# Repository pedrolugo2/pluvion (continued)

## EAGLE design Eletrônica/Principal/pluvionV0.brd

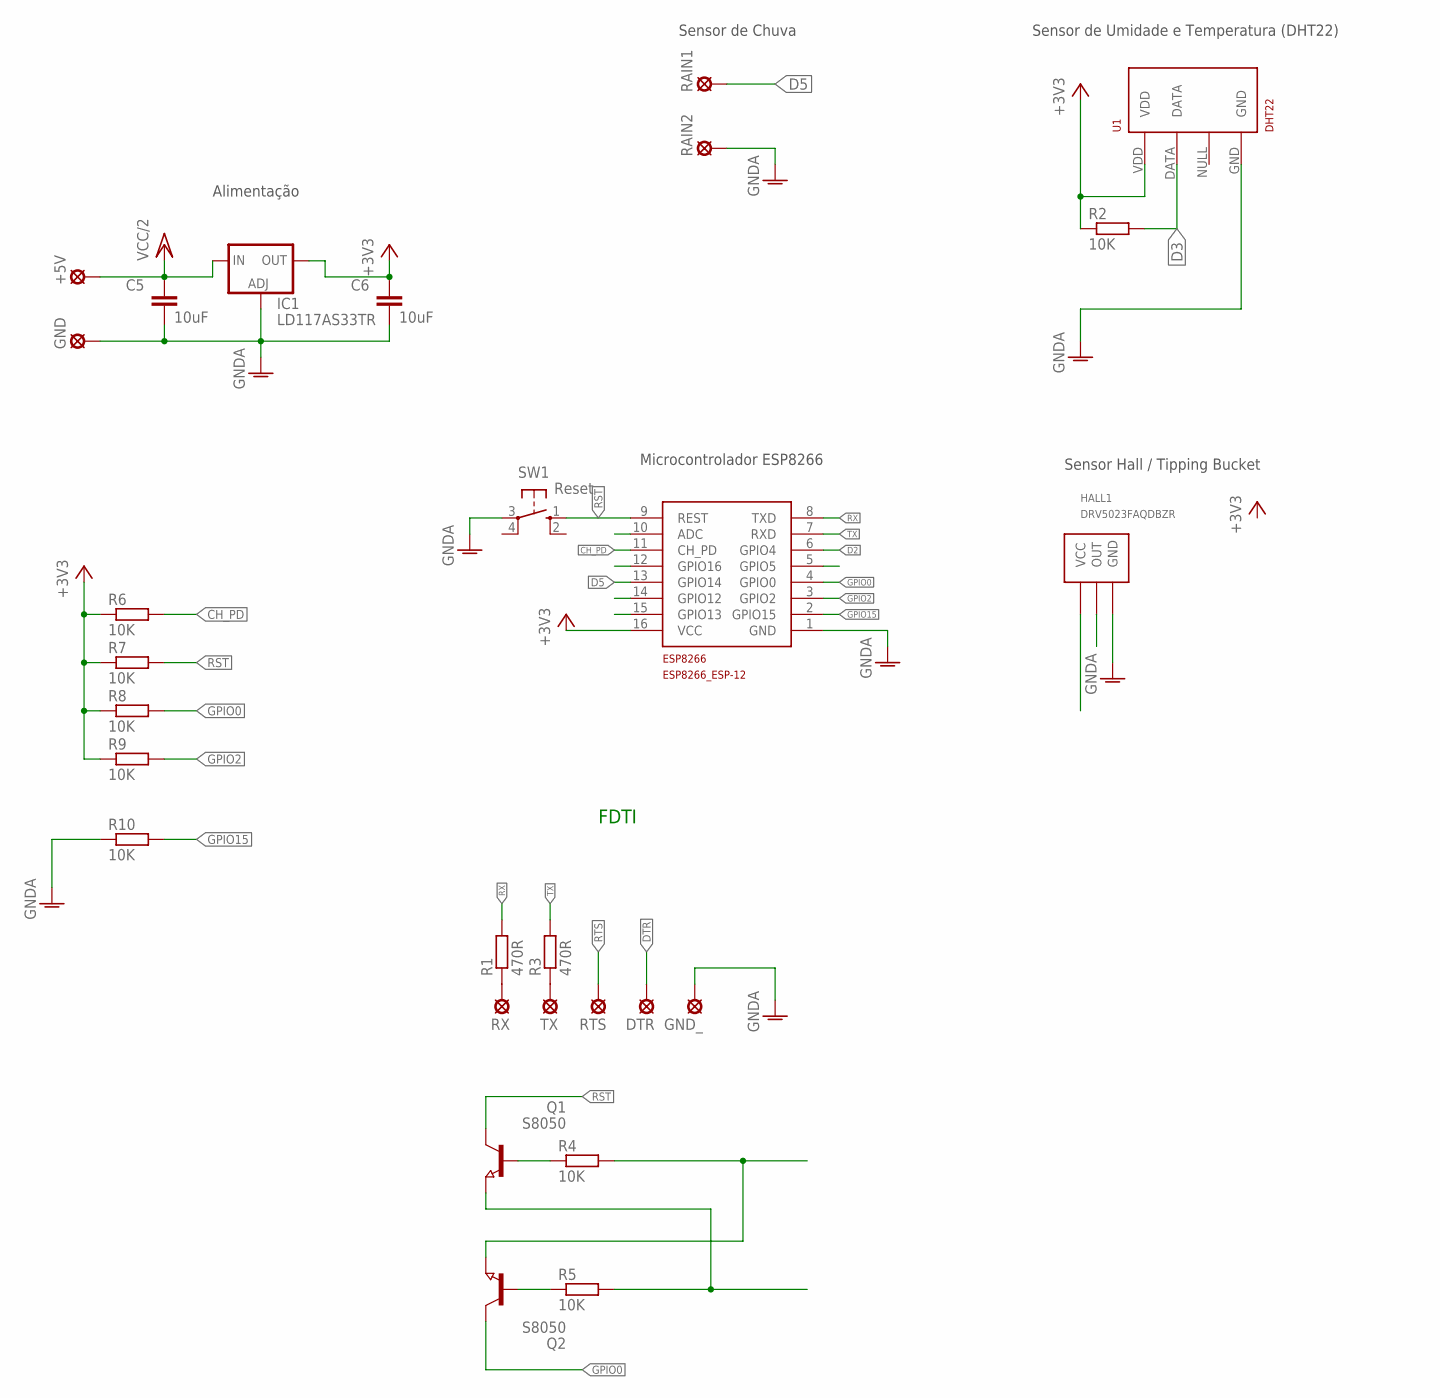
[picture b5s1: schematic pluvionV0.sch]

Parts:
+5V: LSP10
C5, C6: 10uF; C0805K
DTR: LSP10
ESP8266: ESP8266_ESP-12; ESP8266-ESP12
GND: LSP10
GND_: LSP10
HALL1: DRV5023FAQDBZR; SOT23
IC1: LD117AS33TR; SOT223
Q1, Q2: S8050; SOT23
R1, R3: 470R; M1206
R2, R4, R5, R6, R7, R8, R9, R10: 10K; M1206
RAIN1, RAIN2: LSP10
RTS: LSP10
RX: LSP10
SW1: Reset; B3F-10XX
TX: LSP10
U1: DHT22; RHT03_DHT-22/RA

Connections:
+3V3: C6.1, ESP8266.16 (VCC), IC1.4 (OUT), R2.1, R6.1, R7.1, R8.1, R9.1, U1.VDD
CH_PD: ESP8266.11 (CH_PD), R6.2
D2: ESP8266.6 (GPIO4)
D3: R2.2, U1.DATA
D5: ESP8266.13 (GPIO14), RAIN1.MP
DTR: DTR.MP, Q2.2 (E), R4.2
GND: C5.2, C6.2, ESP8266.1 (GND), GND.MP, IC1.1 (ADJ), RAIN2.MP, SW1.3, U1.GND
GNDA: GND_.MP, HALL1.3 (GND), R10.1
GPIO0: ESP8266.4 (GPIO0), Q2.3 (C), R8.2
GPIO2: ESP8266.3 (GPIO2), R9.2
GPIO15: ESP8266.2 (GPIO15), R10.2
unnamed: R1.1, RX.MP
unnamed: Q1.1 (B), R4.1
unnamed: R3.1, TX.MP
unnamed: Q2.1 (B), R5.1
RST: ESP8266.9 (REST), Q1.3 (C), R7.2, SW1.1 (S)
RTS: Q1.2 (E), R5.2, RTS.MP
RX: ESP8266.8 (TXD), R1.2
TX: ESP8266.7 (RXD), R3.2
VCC/2: +5V.MP, C5.1, IC1.3 (IN)

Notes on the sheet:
Sensor de Umidade e Temperatura (DHT22)
Sensor Hall / Tipping Bucket
Sensor de Chuva
Microcontrolador ESP8266
Alimentação
FDTI

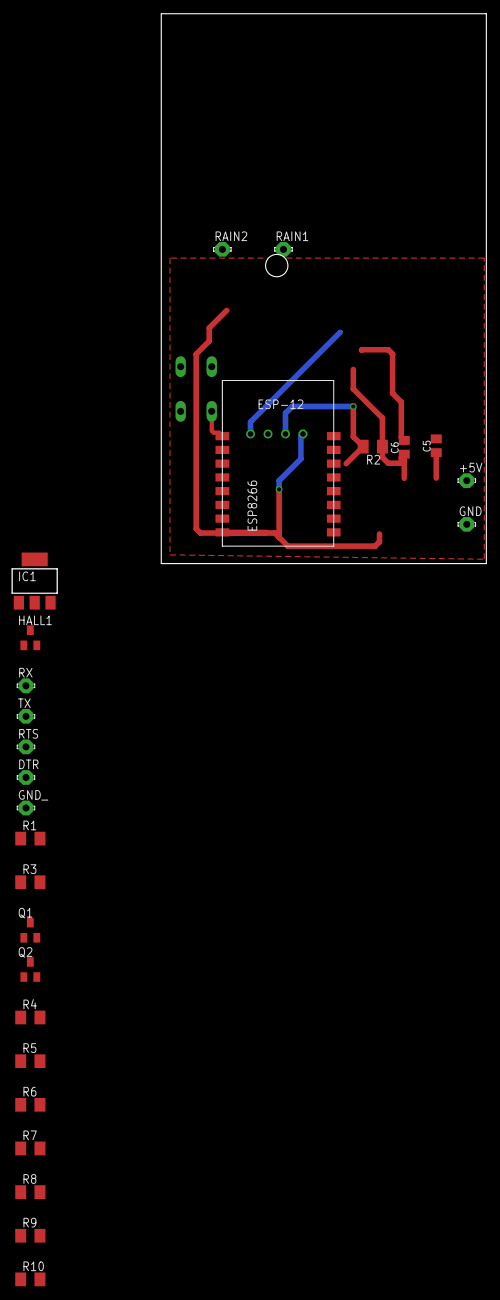
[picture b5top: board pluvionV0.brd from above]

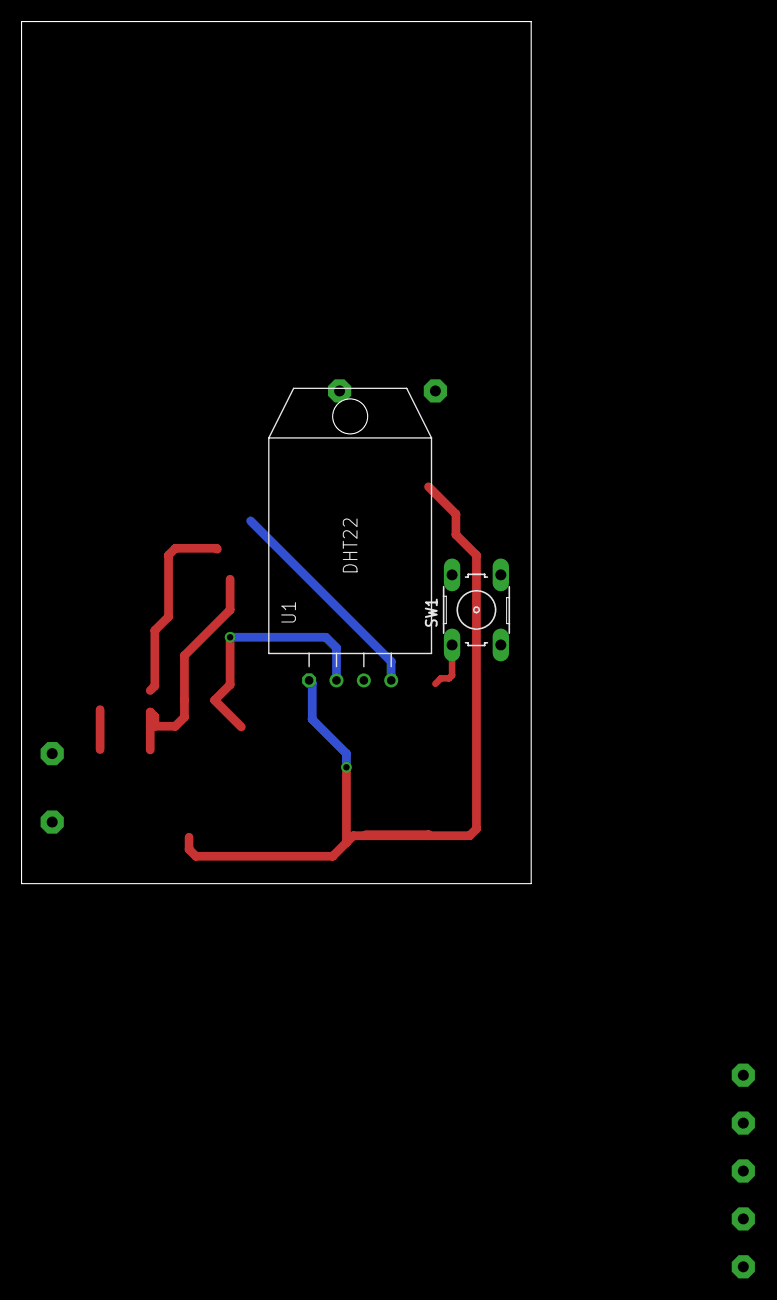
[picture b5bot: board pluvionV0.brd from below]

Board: 2 copper layers, 47.3 x 80.0 mm, 28 parts (2 on the bottom side), 19 nets.

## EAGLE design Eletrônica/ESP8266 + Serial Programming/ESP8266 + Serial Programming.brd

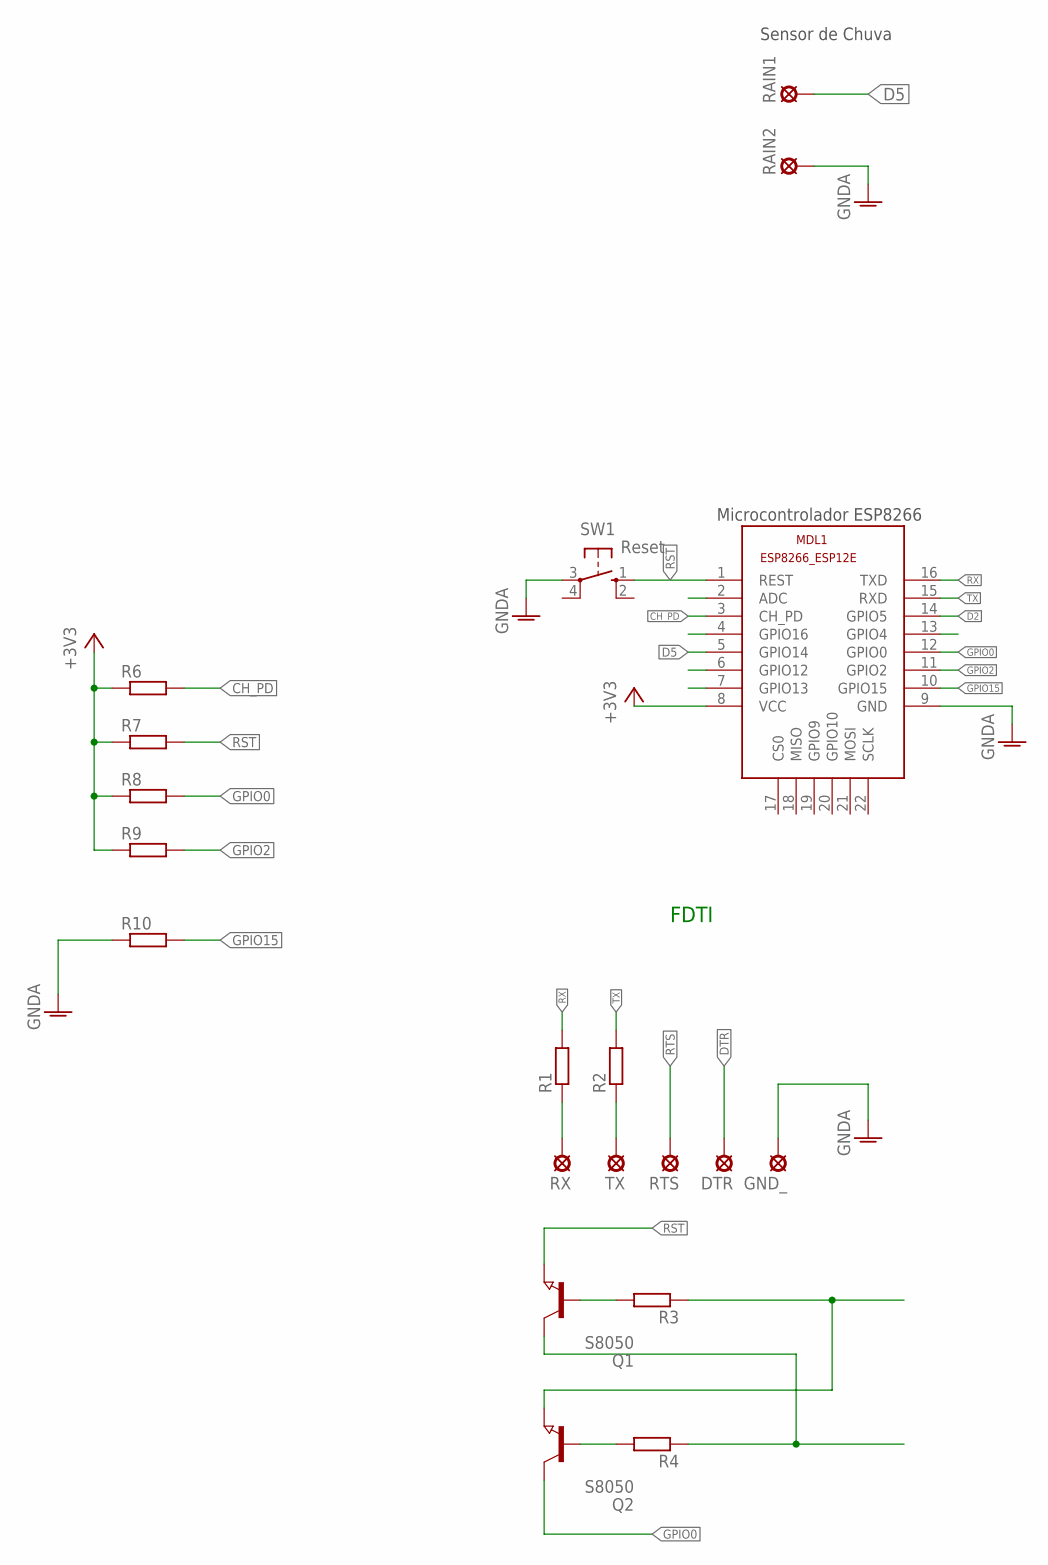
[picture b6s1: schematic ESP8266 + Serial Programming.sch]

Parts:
DTR: LSP10
GND_: LSP10
MDL1: ESP8266-12EESP8266-ESP12E; ESP8266-ESP12E
Q1, Q2: S8050; SOT23
R1, R2, R3, R4, R6, R7, R8, R9, R10: R-EU_R0805; R0805
RAIN1, RAIN2: LSP10
RTS: LSP10
RX: LSP10
SW1: Reset; B3F-10XX
TX: LSP10

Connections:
+3V3: MDL1.8 (VCC), R6.1, R7.1, R8.1, R9.1
CH_PD: MDL1.3 (CH_PD), R6.2
D2: MDL1.14 (GPIO5)
D5: MDL1.5 (GPIO14), RAIN1.MP
DTR: DTR.MP, Q2.2 (E), R3.1
GND: MDL1.9 (GND), RAIN2.MP, SW1.3
GNDA: GND_.MP, R10.1
GPIO0: MDL1.12 (GPIO0), Q2.3 (C), R8.2
GPIO2: MDL1.11 (GPIO2), R9.2
GPIO15: MDL1.10 (GPIO15), R10.2
unnamed: R1.1, RX.MP
unnamed: R2.1, TX.MP
unnamed: Q1.1 (B), R3.2
unnamed: Q2.1 (B), R4.2
RST: MDL1.1 (REST), Q1.2 (E), R7.2, SW1.1 (S)
RTS: Q1.3 (C), R4.1, RTS.MP
RX: MDL1.16 (TXD), R1.2
TX: MDL1.15 (RXD), R2.2

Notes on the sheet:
Sensor de Chuva
Microcontrolador ESP8266
FDTI

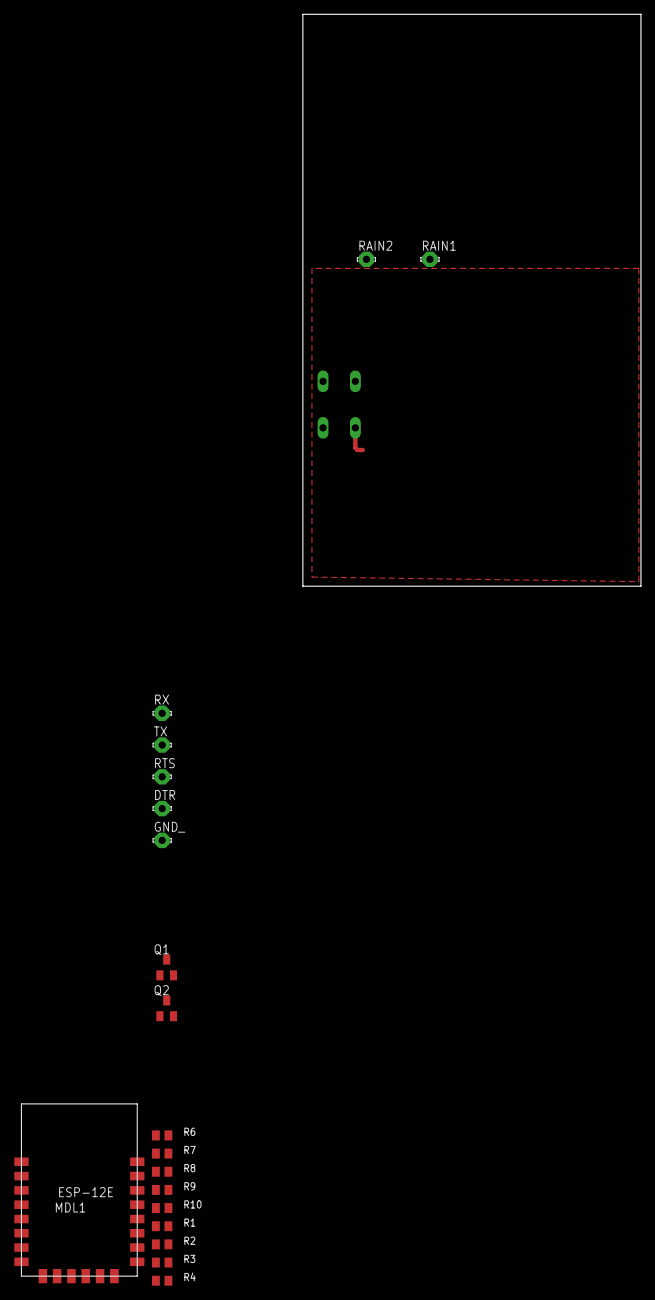
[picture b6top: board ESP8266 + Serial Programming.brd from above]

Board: 2 copper layers, 47.3 x 80.0 mm, 20 parts (1 on the bottom side), 17 nets.

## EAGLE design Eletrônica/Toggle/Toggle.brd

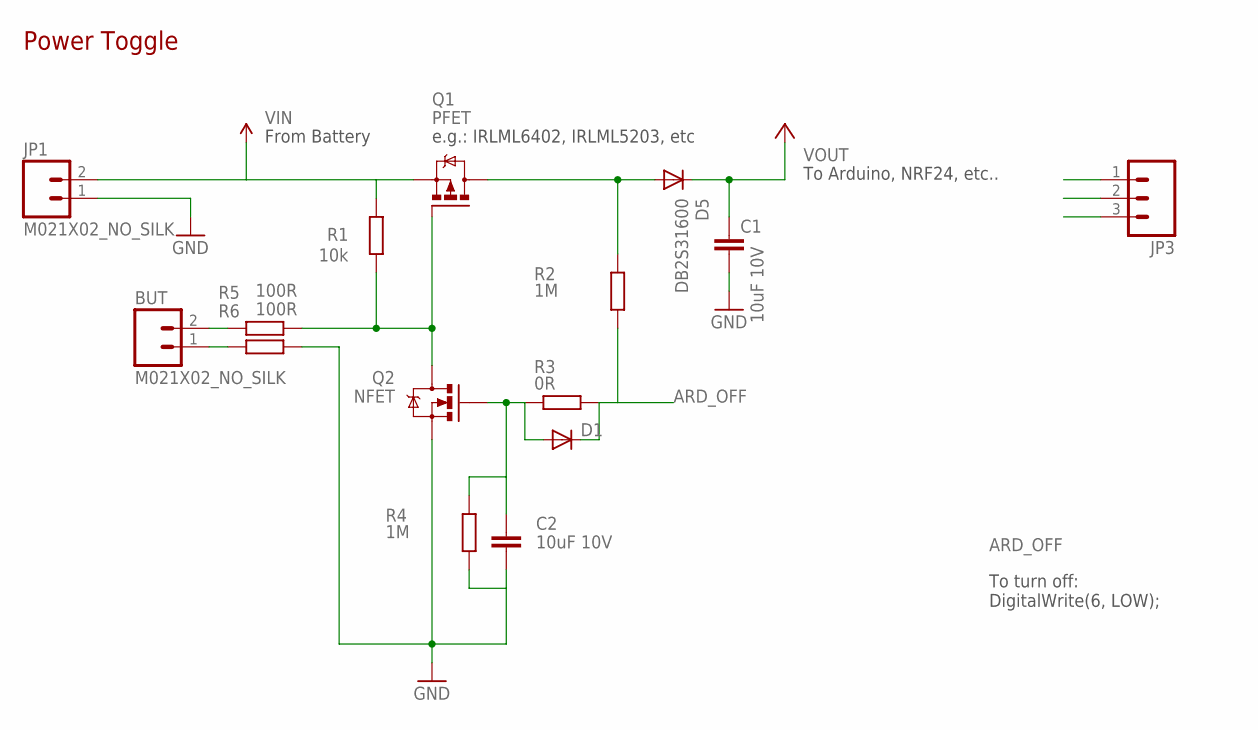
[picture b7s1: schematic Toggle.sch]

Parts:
BUT: M021X02_NO_SILK; 1X02_NO_SILK
C1, C2: 10uF 10V; C0805
D1: DIODESOD523; SOD523
D5: DB2S31600; SMA-DIODE
JP1: M021X02_NO_SILK; 1X02_NO_SILK
JP3: M031X03_NO_SILK; 1X03_NO_SILK
Q1: PFET; MICRO3
Q2: NFET; SOT23
R1: 10k; R0603
R2, R4: 1M; R0603
R3: 0R; R0603
R5, R6: 100R; R0603

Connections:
ARD_OFF: D1.C, JP3.3, R2.1, R3.2
BUTTONS: Q1.1 (G), Q2.3 (D), R1.1, R5.1
GND: C1.2, C2.2, JP1.1, JP3.1, Q2.2 (S), R4.1, R6.1
unnamed: C2.1, D1.A, Q2.1 (G), R3.1, R4.2
unnamed: BUT.2, R5.2
unnamed: D5.A, Q1.3 (D), R2.2
unnamed: BUT.1, R6.2
VIN: JP1.2, Q1.2 (S), R1.2
VOUT: C1.1, D5.C, JP3.2

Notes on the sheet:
e.g.: IRLML6402, IRLML5203, etc
To Arduino, NRF24, etc..
To turn off: DigitalWrite(6, LOW);
From Battery
Power Toggle

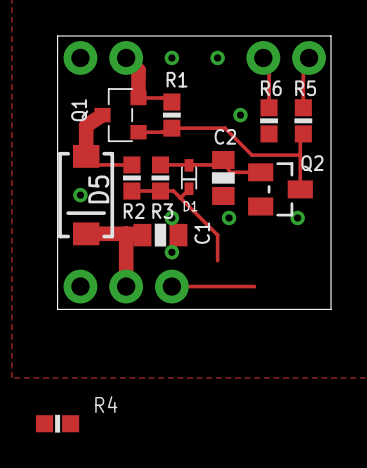
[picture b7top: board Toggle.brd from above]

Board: 2 copper layers, 15.2 x 15.2 mm, 15 parts (0 on the bottom side), 9 nets.

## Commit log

2016-09-13 Reorganizing
2016-09-13 .DS_Store Cleanup
2016-09-13 Eagle .gitignore updates
2016-09-14 1st commit
2016-09-14 .lck added to .gitignore
2016-09-14 Add libraries
2016-09-14 Update schematic
2016-09-14 Toggle updated
2016-09-14 Eagle files
2016-09-14 Eagle Rev A
2016-09-14 Prototype BOM
2016-09-14 Gerber Files
2016-09-18 .b## and .s## added to .gitignore
2016-09-19 Firmware com mudanças e funcionalidades novas
2016-09-20 add DHT library
2016-09-22 Pluvion Rev B for tests
2016-09-22 File rename
2016-09-22 Pluvion 1 Rev C
2016-09-22 Pluvion V2
2016-09-22 Adding schematic images
2016-09-22 Inclusao de montagem mecanica
2016-09-24 Pluvion V2 ready for prototyping
2016-09-29 Shield Update
